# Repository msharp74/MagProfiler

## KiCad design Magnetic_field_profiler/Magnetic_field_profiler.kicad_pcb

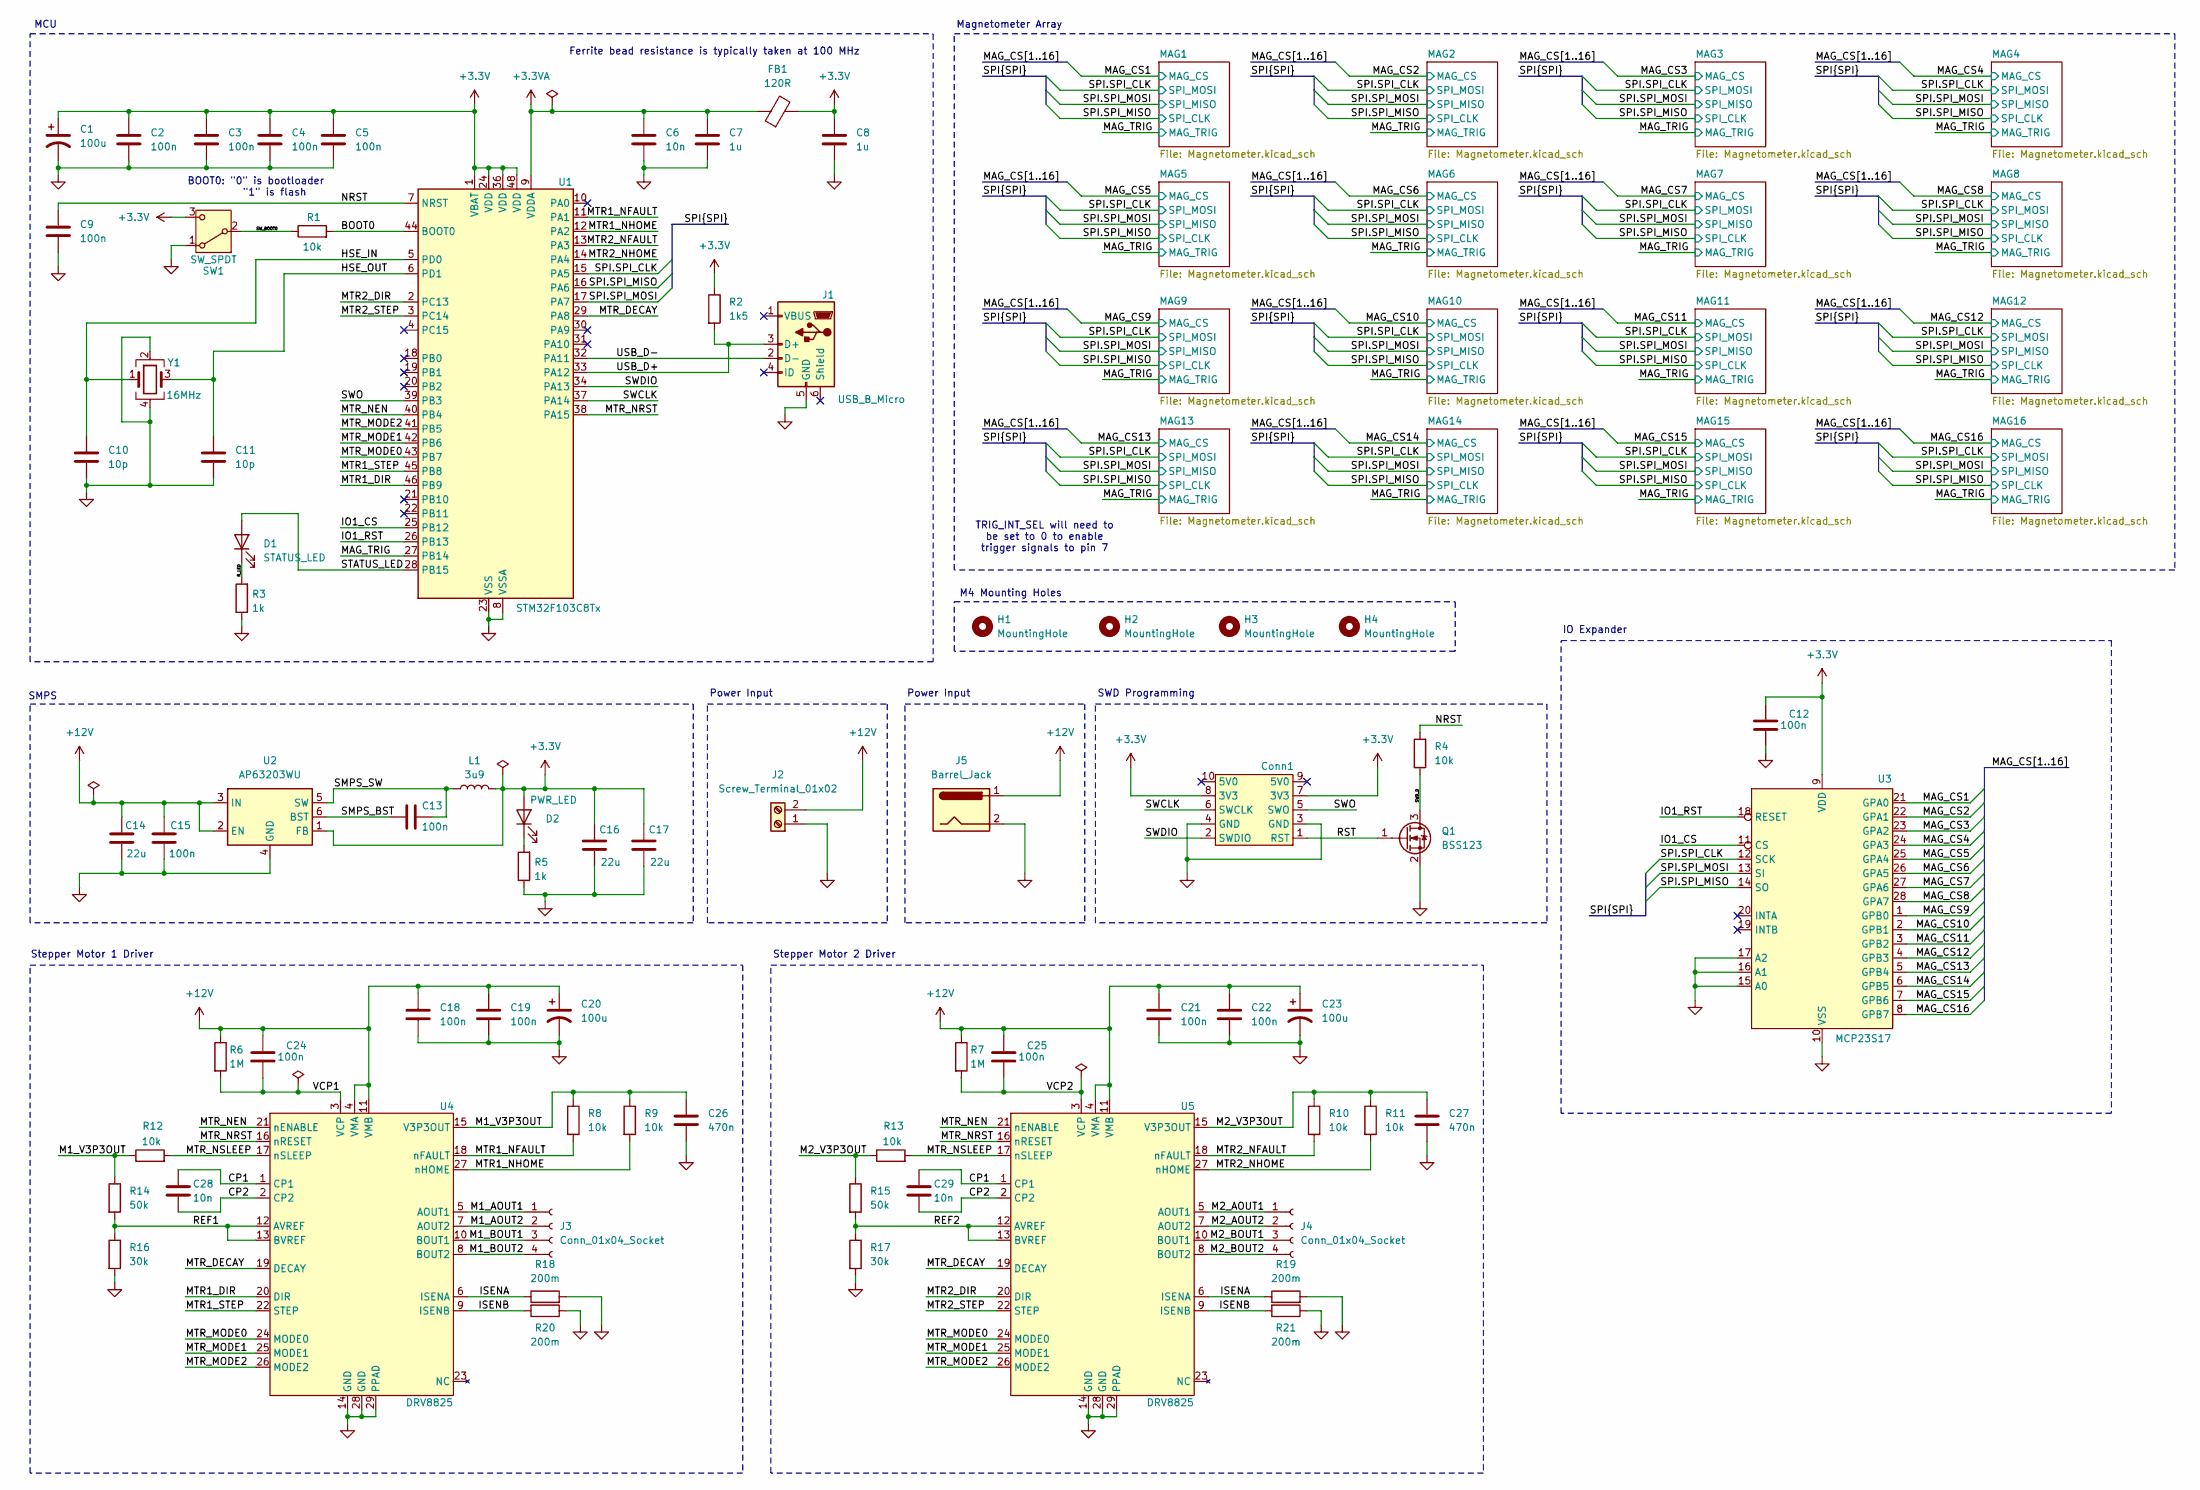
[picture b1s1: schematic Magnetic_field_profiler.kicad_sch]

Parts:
C1, C20, C23: 100u; CP_Radial_D5.0mm_P2.00mm; Manufacturer Part Number 16ZLH100MEFC5X11
C2, C3, C4, C5, C9, C12, C13, C15, C18, C19, C21, C22, C24, C25: 100n; C_0201_0603Metric; Manufacturer Part Number GRM033C81E104KE14D
C6, C28, C29: 10n; C_0201_0603Metric; Manufacturer Part Number GRM033R61E103KA12D
C7, C8: 1u; C_0603_1608Metric; Manufacturer Part Number CC0603KRX5R8BB105
C10, C11: 10p; C_0402_1005Metric; Manufacturer Part Number GRM1555C1H100FA01D
C14, C16, C17: 22u; C_1206_3216Metric; Manufacturer Part Number CL31A226MOCLNNC
C26, C27: 470n; C_0402_1005Metric; Manufacturer Part Number CL21B474KAFNNNG
Conn1: Tag-Connect_TC2050-IDC-FP_2x05_P1.27mm_Vertical
D1: STATUS_LED; LED_0805_2012Metric; Manufacturer Part Number 150080VS75000
D2: PWR_LED; LED_0805_2012Metric; Manufacturer Part Number 150080RS75000
FB1: 120R; L_0805_2012Metric; Manufacturer Part Number BLM18KG121TN1D
H1, H2, H3, H4: MountingHole; MountingHole_3.2mm_M3
J1: USB_B_Micro; USB_Micro-B_Wuerth_629105150521; Manufacturer Part Number 629105150521
J2: Screw_Terminal_01x02; TerminalBlock_Phoenix_MKDS-1,5-2_1x02_P5.00mm_Horizontal; Manufacturer Part Number 1715022
J3, J4: Conn_01x04_Socket; JST_PH_S4B-PH-K_1x04_P2.00mm_Horizontal; Manufacturer Part Number S4B-PH-K-S
J5: Barrel_Jack; BarrelJack_Wuerth_6941xx301002; Manufacturer Part Number 694108301002
L1: 3u9; L_Abracon_ASPI-3012S; Manufacturer Part Number ASPI-3012S-3R9N-T
Q1: BSS123; SOT-23; Manufacturer Part Number BSS123-7-F
R1, R4, R8, R9, R10, R11, R12, R13: 10k; R_0805_2012Metric; Manufacturer Part Number RMCF0805JT10K0
R2: 1k5; R_0402_1005Metric; Manufacturer Part Number RC0805JR-071K5L
R3, R5: 1k; R_0402_1005Metric; Manufacturer Part Number RC0805FR-071KL
R6, R7: 1M; R_0402_1005Metric; Manufacturer Part Number CRGCQ0402J1M0
R14, R15: 50k; R_0402_1005Metric; Manufacturer Part Number CRCW040250K0FKED
R16, R17: 30k; R_0402_1005Metric; Manufacturer Part Number RC0402FR-0730KL
R18, R19, R20, R21: 200m; R_1206_3216Metric; Manufacturer Part Number CSR1206FKR200
SW1: SW_SPDT; SW_SPDT_PCM12; Manufacturer Part Number B3F-1000
U1: STM32F103C8Tx; LQFP-48_7x7mm_P0.5mm; Manufacturer Part Number STM32F103C8T6TR
U2: AP63203WU; TSOT-23-6; Manufacturer Part Number AP63203WU-7
U3: MCP23S17; SSOP-28_5.3x10.2mm_P0.65mm; Manufacturer Part Number MCP23S17T-E/SS
U4, U5: DRV8825; TSSOP-28-1EP_4.4x9.7mm_P0.65mm; Manufacturer Part Number DRV8825PWPR
Y1: 16MHz; Crystal_SMD_3225-4Pin_3.2x2.5mm

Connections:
+3.3V: C1.1, C2.1, C3.1, C4.1, C5.1, C8.1, C12.1, C16.1, C17.1, Conn1.7 (3V3), Conn1.8 (3V3), D2.2 (A), FB1.2, L1.2, R2.1, SW1.3 (C), U1.1 (VBAT), U1.24 (VDD), U1.36 (VDD), U1.48 (VDD), U2.1 (FB), U3.9 (VDD); also elsewhere on the board
+3.3VA: C6.1, C7.1, FB1.1, U1.9 (VDDA)
+12V: C14.2, C15.1, C18.1, C19.1, C20.1, C21.1, C22.1, C23.1, C24.1, C25.1, J2.2, J5.1, R6.1, R7.1, U2.2 (EN), U2.3 (IN), U4.4 (VMA), U4.11 (VMB), U5.4 (VMA), U5.11 (VMB)
/BOOT0: R1.2, U1.44 (BOOT0)
/CP1: C28.1, C29.1, U4.1 (CP1), U5.1 (CP1)
/CP2: C28.2, C29.2, U4.2 (CP2), U5.2 (CP2)
/HSE_IN: C10.1, U1.5 (PD0), Y1.1
/HSE_OUT: C11.1, U1.6 (PD1), Y1.3
/IO1_CS: U1.25 (PB12), U3.11 (CS)
/IO1_RST: U1.26 (PB13), U3.18 (RESET)
/ISENA: R18.1, R19.1, U4.6 (ISENA), U5.6 (ISENA)
/ISENB: R20.2, R21.2, U4.9 (ISENB), U5.9 (ISENB)
/M1_AOUT1: J3.1, U4.5 (AOUT1)
/M1_AOUT2: J3.2, U4.7 (AOUT2)
/M1_BOUT1: J3.3, U4.10 (BOUT1)
/M1_BOUT2: J3.4, U4.8 (BOUT2)
/M1_V3P3OUT: C26.1, R8.1, R9.1, R12.1, R14.1, U4.15 (V3P3OUT)
/M2_AOUT1: J4.1, U5.5 (AOUT1)
/M2_AOUT2: J4.2, U5.7 (AOUT2)
/M2_BOUT1: J4.3, U5.10 (BOUT1)
/M2_BOUT2: J4.4, U5.8 (BOUT2)
/M2_V3P3OUT: C27.1, R10.1, R11.1, R13.1, R15.1, U5.15 (V3P3OUT)
/MAG_CS1: U3.21 (GPA0); also elsewhere on the board
/MAG_CS2: U3.22 (GPA1); also elsewhere on the board
/MAG_CS3: U3.23 (GPA2); also elsewhere on the board
/MAG_CS4: U3.24 (GPA3); also elsewhere on the board
/MAG_CS5: U3.25 (GPA4); also elsewhere on the board
/MAG_CS6: U3.26 (GPA5); also elsewhere on the board
/MAG_CS7: U3.27 (GPA6); also elsewhere on the board
/MAG_CS8: U3.28 (GPA7); also elsewhere on the board
/MAG_CS9: U3.1 (GPB0); also elsewhere on the board
/MAG_CS10: U3.2 (GPB1); also elsewhere on the board
/MAG_CS11: U3.3 (GPB2); also elsewhere on the board
/MAG_CS12: U3.4 (GPB3); also elsewhere on the board
/MAG_CS13: U3.5 (GPB4); also elsewhere on the board
/MAG_CS14: U3.6 (GPB5); also elsewhere on the board
/MAG_CS15: U3.7 (GPB6); also elsewhere on the board
/MAG_CS16: U3.8 (GPB7); also elsewhere on the board
/MAG_TRIG: U1.27 (PB14); also elsewhere on the board
/MTR1_DIR: U1.46 (PB9), U4.20 (DIR)
/MTR1_NFAULT: R8.2, U1.11 (PA1), U4.18 (nFAULT)
/MTR1_NHOME: R9.2, U1.12 (PA2), U4.27 (nHOME)
/MTR1_STEP: U1.45 (PB8), U4.22 (STEP)
/MTR2_DIR: U1.2 (PC13), U5.20 (DIR)
/MTR2_NFAULT: R10.2, U1.13 (PA3), U5.18 (nFAULT)
/MTR2_NHOME: R11.2, U1.14 (PA4), U5.27 (nHOME)
/MTR2_STEP: U1.3 (PC14), U5.22 (STEP)
/MTR_DECAY: U1.29 (PA8), U4.19 (DECAY), U5.19 (DECAY)
/MTR_MODE0: U1.43 (PB7), U4.24 (MODE0), U5.24 (MODE0)
/MTR_MODE1: U1.42 (PB6), U4.25 (MODE1), U5.25 (MODE1)
/MTR_MODE2: U1.41 (PB5), U4.26 (MODE2), U5.26 (MODE2)
/MTR_NEN: U1.40 (PB4), U4.21 (nENABLE), U5.21 (nENABLE)
/MTR_NRST: U1.38 (PA15), U4.16 (nRESET), U5.16 (nRESET)
/MTR_NSLEEP: R12.2, R13.2, U4.17 (nSLEEP), U5.17 (nSLEEP)
/NRST: C9.1, R4.2, U1.7 (NRST)
/REF1: R14.2, R16.1, U4.12 (AVREF), U4.13 (BVREF)
/REF2: R15.2, R17.1, U5.12 (AVREF), U5.13 (BVREF)
/RST: Conn1.1 (RST), Q1.1 (G)
/R_LED: D1.1 (K), R3.2
/SMPS_BST: C13.1, U2.6 (BST)
/SMPS_SW: C13.2, L1.1, U2.5 (SW)
/SPI.SPI_CLK: U1.15 (PA5), U3.12 (SCK); also elsewhere on the board
/SPI.SPI_MISO: U1.16 (PA6), U3.14 (SO); also elsewhere on the board
/SPI.SPI_MOSI: U1.17 (PA7), U3.13 (SI); also elsewhere on the board
/STATUS_LED: D1.2 (A), U1.28 (PB15)
/SWCLK: Conn1.6 (SWCLK), U1.37 (PA14)
/SWDIO: Conn1.2 (SWDIO), U1.34 (PA13)
/SWD_D: Q1.3 (D), R4.1
/SWO: Conn1.5 (SWO), U1.39 (PB3)
/SW_BOOT0: R1.1, SW1.2 (B)
/USB_D+: J1.3 (D+), R2.2, U1.33 (PA12)
/USB_D-: J1.2 (D-), U1.32 (PA11)
/VCP1: C24.2, R6.2, U4.3 (VCP)
/VCP2: C25.2, R7.2, U5.3 (VCP)
GND: C1.2, C2.2, C3.2, C4.2, C5.2, C6.2, C7.2, C8.2, C9.2, C10.2, C11.2, C12.2, C14.1, C15.2, C16.2, C17.2, C18.2, C19.2, C20.2, C21.2, C22.2, C23.2, C26.2, C27.2, Conn1.3 (GND), Conn1.4 (GND), J1.5 (GND), J2.1, J5.2, Q1.2 (S), R3.1, R5.1, R16.2, R17.2, R18.2, R19.2, R20.1, R21.1, SW1.1 (A), U1.8 (VSSA), U1.23 (VSS), U1.35 (VSS), U1.47 (VSS), U2.4 (GND), U3.10 (VSS), U3.15 (A0), U3.16 (A1), U3.17 (A2), U4.14 (GND), U4.28 (GND), U4.29 (PPAD), U5.14 (GND), U5.28 (GND), U5.29 (PPAD), Y1.2, Y1.4; also elsewhere on the board
unnamed: D2.1 (K), R5.2

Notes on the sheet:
TRIG_INT_SEL will need to be set to 0 to enable trigger signals to pin 7
SMPS
Magnetometer Array
BOOT0: "0" is bootloader "1" is flash
MCU
Stepper Motor 1 Driver
Ferrite bead resistance is typically taken at 100 MHz
SWD Programming
Power Input
M4 Mounting Holes
Stepper Motor 2 Driver
IO Expander

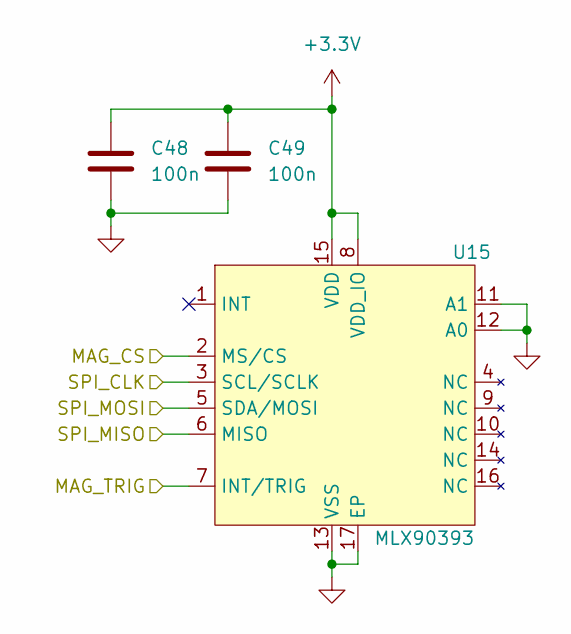
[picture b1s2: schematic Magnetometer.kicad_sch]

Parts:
C48, C49: 100n; C_0201_0603Metric; Manufacturer Part Number GRM033C81E104KE14D
U15: MLX90393; QFN-16-1EP_3x3mm_P0.5mm_EP1.75x1.75mm_ThermalVias; Manufacturer Part Number MLX90393SLW-ABA-011-RE

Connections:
+3.3V: C48.1, C49.1, U15.8 (VDD_IO), U15.15 (VDD); also elsewhere on the board
/MAG_CS10: U15.2 (MS/CS); also elsewhere on the board
/MAG_TRIG: U15.7 (INT/TRIG); also elsewhere on the board
/SPI.SPI_CLK: U15.5 (SDA/MOSI); also elsewhere on the board
/SPI.SPI_MISO: U15.3 (SCL/SCLK); also elsewhere on the board
/SPI.SPI_MOSI: U15.6 (MISO); also elsewhere on the board
GND: C48.2, C49.2, U15.11 (A1), U15.12 (A0), U15.13 (VSS), U15.17 (EP); also elsewhere on the board

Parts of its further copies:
C30, C31, C32, C33, C34, C35, C36, C37, C38, C39, C40, C41, C42, C43, C44, C45, C46, C47, C50, C51, C52, C53, C54, C55, C56, C57, C58, C59, C60, C61: 100n; C_0201_0603Metric; Manufacturer Part Number GRM033C81E104KE14D
U6, U7, U8, U9, U10, U11, U12, U13, U14, U16, U17, U18, U19, U20, U21: MLX90393; QFN-16-1EP_3x3mm_P0.5mm_EP1.75x1.75mm_ThermalVias; Manufacturer Part Number MLX90393SLW-ABA-011-RE

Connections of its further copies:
+3.3V: C30.1, C31.1, C32.1, C33.1, C34.1, C35.1, C36.1, C37.1, C38.1, C39.1, C40.1, C41.1, C42.1, C43.1, C44.1, C45.1, C46.1, C47.1, C50.1, C51.1, C52.1, C53.1, C54.1, C55.1, C56.1, C57.1, C58.1, C59.1, C60.1, C61.1, U6.8 (VDD_IO), U6.15 (VDD), U7.8 (VDD_IO), U7.15 (VDD), U8.8 (VDD_IO), U8.15 (VDD), U9.8 (VDD_IO), U9.15 (VDD), U10.8 (VDD_IO), U10.15 (VDD), U11.8 (VDD_IO), U11.15 (VDD), U12.8 (VDD_IO), U12.15 (VDD), U13.8 (VDD_IO), U13.15 (VDD), U14.8 (VDD_IO), U14.15 (VDD), U16.8 (VDD_IO), U16.15 (VDD), U17.8 (VDD_IO), U17.15 (VDD), U18.8 (VDD_IO), U18.15 (VDD), U19.8 (VDD_IO), U19.15 (VDD), U20.8 (VDD_IO), U20.15 (VDD), U21.8 (VDD_IO), U21.15 (VDD); also elsewhere on the board
/MAG_CS1: U6.2 (MS/CS); also elsewhere on the board
/MAG_CS2: U7.2 (MS/CS); also elsewhere on the board
/MAG_CS3: U8.2 (MS/CS); also elsewhere on the board
/MAG_CS4: U9.2 (MS/CS); also elsewhere on the board
/MAG_CS5: U10.2 (MS/CS); also elsewhere on the board
/MAG_CS6: U11.2 (MS/CS); also elsewhere on the board
/MAG_CS7: U12.2 (MS/CS); also elsewhere on the board
/MAG_CS8: U13.2 (MS/CS); also elsewhere on the board
/MAG_CS9: U14.2 (MS/CS); also elsewhere on the board
/MAG_CS11: U16.2 (MS/CS); also elsewhere on the board
/MAG_CS12: U17.2 (MS/CS); also elsewhere on the board
/MAG_CS13: U18.2 (MS/CS); also elsewhere on the board
/MAG_CS14: U19.2 (MS/CS); also elsewhere on the board
/MAG_CS15: U20.2 (MS/CS); also elsewhere on the board
/MAG_CS16: U21.2 (MS/CS); also elsewhere on the board
/MAG_TRIG: U6.7 (INT/TRIG), U7.7 (INT/TRIG), U8.7 (INT/TRIG), U9.7 (INT/TRIG), U10.7 (INT/TRIG), U11.7 (INT/TRIG), U12.7 (INT/TRIG), U13.7 (INT/TRIG), U14.7 (INT/TRIG), U16.7 (INT/TRIG), U17.7 (INT/TRIG), U18.7 (INT/TRIG), U19.7 (INT/TRIG), U20.7 (INT/TRIG), U21.7 (INT/TRIG); also elsewhere on the board
/SPI.SPI_CLK: U6.5 (SDA/MOSI), U7.5 (SDA/MOSI), U8.5 (SDA/MOSI), U9.5 (SDA/MOSI), U10.5 (SDA/MOSI), U11.5 (SDA/MOSI), U12.5 (SDA/MOSI), U13.5 (SDA/MOSI), U14.5 (SDA/MOSI), U16.5 (SDA/MOSI), U17.5 (SDA/MOSI), U18.5 (SDA/MOSI), U19.5 (SDA/MOSI), U20.5 (SDA/MOSI), U21.5 (SDA/MOSI); also elsewhere on the board
/SPI.SPI_MISO: U6.3 (SCL/SCLK), U7.3 (SCL/SCLK), U8.3 (SCL/SCLK), U9.3 (SCL/SCLK), U10.3 (SCL/SCLK), U11.3 (SCL/SCLK), U12.3 (SCL/SCLK), U13.3 (SCL/SCLK), U14.3 (SCL/SCLK), U16.3 (SCL/SCLK), U17.3 (SCL/SCLK), U18.3 (SCL/SCLK), U19.3 (SCL/SCLK), U20.3 (SCL/SCLK), U21.3 (SCL/SCLK); also elsewhere on the board
/SPI.SPI_MOSI: U6.6 (MISO), U7.6 (MISO), U8.6 (MISO), U9.6 (MISO), U10.6 (MISO), U11.6 (MISO), U12.6 (MISO), U13.6 (MISO), U14.6 (MISO), U16.6 (MISO), U17.6 (MISO), U18.6 (MISO), U19.6 (MISO), U20.6 (MISO), U21.6 (MISO); also elsewhere on the board
GND: C30.2, C31.2, C32.2, C33.2, C34.2, C35.2, C36.2, C37.2, C38.2, C39.2, C40.2, C41.2, C42.2, C43.2, C44.2, C45.2, C46.2, C47.2, C50.2, C51.2, C52.2, C53.2, C54.2, C55.2, C56.2, C57.2, C58.2, C59.2, C60.2, C61.2, U6.11 (A1), U6.12 (A0), U6.13 (VSS), U6.17 (EP), U7.11 (A1), U7.12 (A0), U7.13 (VSS), U7.17 (EP), U8.11 (A1), U8.12 (A0), U8.13 (VSS), U8.17 (EP), U9.11 (A1), U9.12 (A0), U9.13 (VSS), U9.17 (EP), U10.11 (A1), U10.12 (A0), U10.13 (VSS), U10.17 (EP), U11.11 (A1), U11.12 (A0), U11.13 (VSS), U11.17 (EP), U12.11 (A1), U12.12 (A0), U12.13 (VSS), U12.17 (EP), U13.11 (A1), U13.12 (A0), U13.13 (VSS), U13.17 (EP), U14.11 (A1), U14.12 (A0), U14.13 (VSS), U14.17 (EP), U16.11 (A1), U16.12 (A0), U16.13 (VSS), U16.17 (EP), U17.11 (A1), U17.12 (A0), U17.13 (VSS), U17.17 (EP), U18.11 (A1), U18.12 (A0), U18.13 (VSS), U18.17 (EP), U19.11 (A1), U19.12 (A0), U19.13 (VSS), U19.17 (EP), U20.11 (A1), U20.12 (A0), U20.13 (VSS), U20.17 (EP), U21.11 (A1), U21.12 (A0), U21.13 (VSS), U21.17 (EP); also elsewhere on the board

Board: 4 copper layers, 120 parts (0 on the bottom side), 76 nets, no tracks yet.

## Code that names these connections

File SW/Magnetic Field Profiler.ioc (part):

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Mcu.Name=STM32F103C(8-B)Tx
Mcu.Package=LQFP48
Mcu.UserName=STM32F103C8Tx
PA1.GPIOParameters=GPIO_Label
PA1.GPIO_Label=MTR1_NFAULT
PA1.Signal=GPIO_Input
PA11.Mode=Device
PA11.Signal=USB_DM
PA12.Mode=Device
PA12.Signal=USB_DP
PA13.Mode=Trace_Asynchronous_SW
PA13.Signal=SYS_JTMS-SWDIO
PA14.Mode=Trace_Asynchronous_SW
PA14.Signal=SYS_JTCK-SWCLK
PA15.GPIOParameters=GPIO_Label
PA15.GPIO_Label=MTR_NRST
PA15.Signal=GPIO_Output
PA2.GPIOParameters=GPIO_Label
PA2.GPIO_Label=MTR1_NHOME
PA2.Signal=GPIO_Input
PA3.GPIOParameters=GPIO_Label
PA3.GPIO_Label=MTR2_NFAULT
PA3.Signal=GPIO_Input
PA4.GPIOParameters=GPIO_Label
PA4.GPIO_Label=MTR2_NHOME
PA4.Signal=GPIO_Input
PA5.Mode=Full_Duplex_Master
PA5.Signal=SPI1_SCK
PA6.Mode=Full_Duplex_Master
PA6.Signal=SPI1_MISO
PA7.Mode=Full_Duplex_Master
PA7.Signal=SPI1_MOSI
PA8.GPIOParameters=GPIO_Label
PA8.GPIO_Label=MTR_DECAY
PA8.Signal=GPIO_Output
PB12.GPIOParameters=GPIO_Label
PB12.GPIO_Label=IO_CS
PB12.Signal=GPIO_Output
PB13.GPIOParameters=GPIO_Label
PB13.GPIO_Label=IO_RST
PB13.Signal=GPIO_Output
PB14.GPIOParameters=GPIO_Label
PB14.GPIO_Label=MAG_TRIG
PB14.Signal=GPIO_Output
PB15.GPIOParameters=GPIO_Label
PB15.GPIO_Label=STATUS_LED
PB15.Signal=GPIO_Output
PB3.Mode=Trace_Asynchronous_SW
PB3.Signal=SYS_JTDO-TRACESWO
PB4.GPIOParameters=GPIO_Label
PB4.GPIO_Label=MTR_NEN
PB4.Signal=GPIO_Output
PB5.GPIOParameters=GPIO_Label
PB5.GPIO_Label=MTR_MODE2
PB5.Signal=GPIO_Output
PB6.GPIOParameters=GPIO_Label
PB6.GPIO_Label=MTR_MODE1
PB6.Signal=GPIO_Output
PB7.GPIOParameters=GPIO_Label
PB7.GPIO_Label=MTR_MODE0
PB7.Signal=GPIO_Output
PB8.GPIOParameters=GPIO_Label
PB8.GPIO_Label=MTR1_STEP
PB8.Signal=GPIO_Output
PB9.GPIOParameters=GPIO_Label
PB9.GPIO_Label=MTR1_DIR
PB9.Signal=GPIO_Output
PC13-TAMPER-RTC.GPIOParameters=GPIO_Label
PC13-TAMPER-RTC.GPIO_Label=MTR2_DIR
PC13-TAMPER-RTC.Signal=GPIO_Output
PC14-OSC32_IN.GPIOParameters=GPIO_Label
PC14-OSC32_IN.GPIO_Label=MTR2_STEP
PC14-OSC32_IN.Signal=GPIO_Output
PD0-OSC_IN.Mode=HSE-External-Oscillator
PD0-OSC_IN.Signal=RCC_OSC_IN
PD1-OSC_OUT.Mode=HSE-External-Oscillator
PD1-OSC_OUT.Signal=RCC_OSC_OUT
RCC.HSE_VALUE=16000000
board=custom

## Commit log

2024-08-12 SMPS Added, Edge Cuts Modified
2024-08-12 Added SMPS Datasheet
2024-08-13 Updated documentation
2024-08-14 Added SMPS and removed LDO
2024-08-15 Edge cuts updated
2024-08-17 PCB Updates and Second Motor Support
2024-10-08 Symbol Properties Edits
2024-10-09 MCU I2C configuration
2024-10-10 Created IO Expander Symbol
2024-10-14 Footprint creation
2024-10-15 IO expander wchematic and footprint updated. Adjusted the schematic representation of the magnetometer array.
2024-10-15 Added IO expander symbol and began connections
2024-10-16 IO expander connections complete and PCB layout restarted
2024-10-17 Swapping MCU IOs and defining netclasses
2024-10-22 Added status LEDs, began updating netclass trace widths
2024-10-23 BOM Information Update
2024-10-29 Adding part descriptions
2024-10-31 DC-DC converter rework
2024-11-01 Continued adding component description and sourcing information
2024-11-02 Initial PCB layout
2024-12-19 Catch Up
2024-12-19 Arduino Stepper Test Program
2024-12-23 Arduino Initial Commit
2024-12-26 First working rev
2024-12-27 added position tracking for motors
2024-12-29 began updating structure of objects
2024-12-29 restructuring carriage object
2024-12-30 adding position tracking
2025-01-02 finished restructuing motor and carriage classes. fixed incorrect angular positioning
2025-01-14 adding functionality to move carriage to specific position
2025-02-11 Added control over motor controller decay line
2025-02-12 PCB Review
2025-02-13 Initial component placement
